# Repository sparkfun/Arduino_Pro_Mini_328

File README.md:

Arduino Pro Mini 328
====================

<table class="table table-hover table-striped table-bordered">
  <tr align="center">
   <td></td>
   <td></td>
  </tr>
  <tr align="center">
    <td><i>Arduino Pro Mini 328 - 5V/16MHz [<a href="https://www.sparkfun.com/products/11113">DEV-11113</a>]</i></td>
    <td><i>Arduino Pro Mini 328 - 3.3V/8MHz [<a href="https://www.sparkfun.com/products/11114">DEV-11114</a>]</i></td>
  </tr>
</table>

SparkFun's Arduino Pro Mini 328 is a bare bones super small Arduino compatible development board. This hardware is used for both the 3.3V/8MHz and the 5V/16MHz versions. 

Both of these products use the same PCB, but are populated with unique voltage regulators and resonators.

Repository Contents
-------------------
* **/Documentation** - SVG and PDF datasheets for the Pro Mini
* **/Hardware** - Eagle design files (Schematic and Board)
* **/Production** - Test bed files and production panel files

Documentation
--------------
* **[Hookup Guide](https://learn.sparkfun.com/tutorials/using-the-arduino-pro-mini-33v)** - Basic hookup guide for the Arduino Pro Mini 3.3V/8MHz. It can be used as a guide with the 5V. The only difference when following the tutorial is selecting the board definition in the Arduino IDE and the voltage levels.

Product Versions
----------------
* [DEV-11113](https://www.sparkfun.com/products/11113)- 5V/16MHz Pro Mini
* [DEV-15254](https://www.sparkfun.com/products/15254)- 5V/16MHz Pro Mini Starter Kit
* [DEV-11114](https://www.sparkfun.com/products/11114)- 3.3V/8MHz Pro Mini
* [DEV-15257](https://www.sparkfun.com/products/15257)- 3.3V/8MHz Pro Mini Starter Kit 

License Information
-------------------
The hardware is released under [Creative Commons Share-alike 3.0](http://creativecommons.org/licenses/by-sa/3.0/).  

Hardware authors: Original Arduino Mini design by Team Arduino

Pro Mini design by Nathan Seidle @ SparkFun Electonics

Revision work by Pete Lewis @ SparkFun Electonics  

Distributed as-is; no warranty is given.

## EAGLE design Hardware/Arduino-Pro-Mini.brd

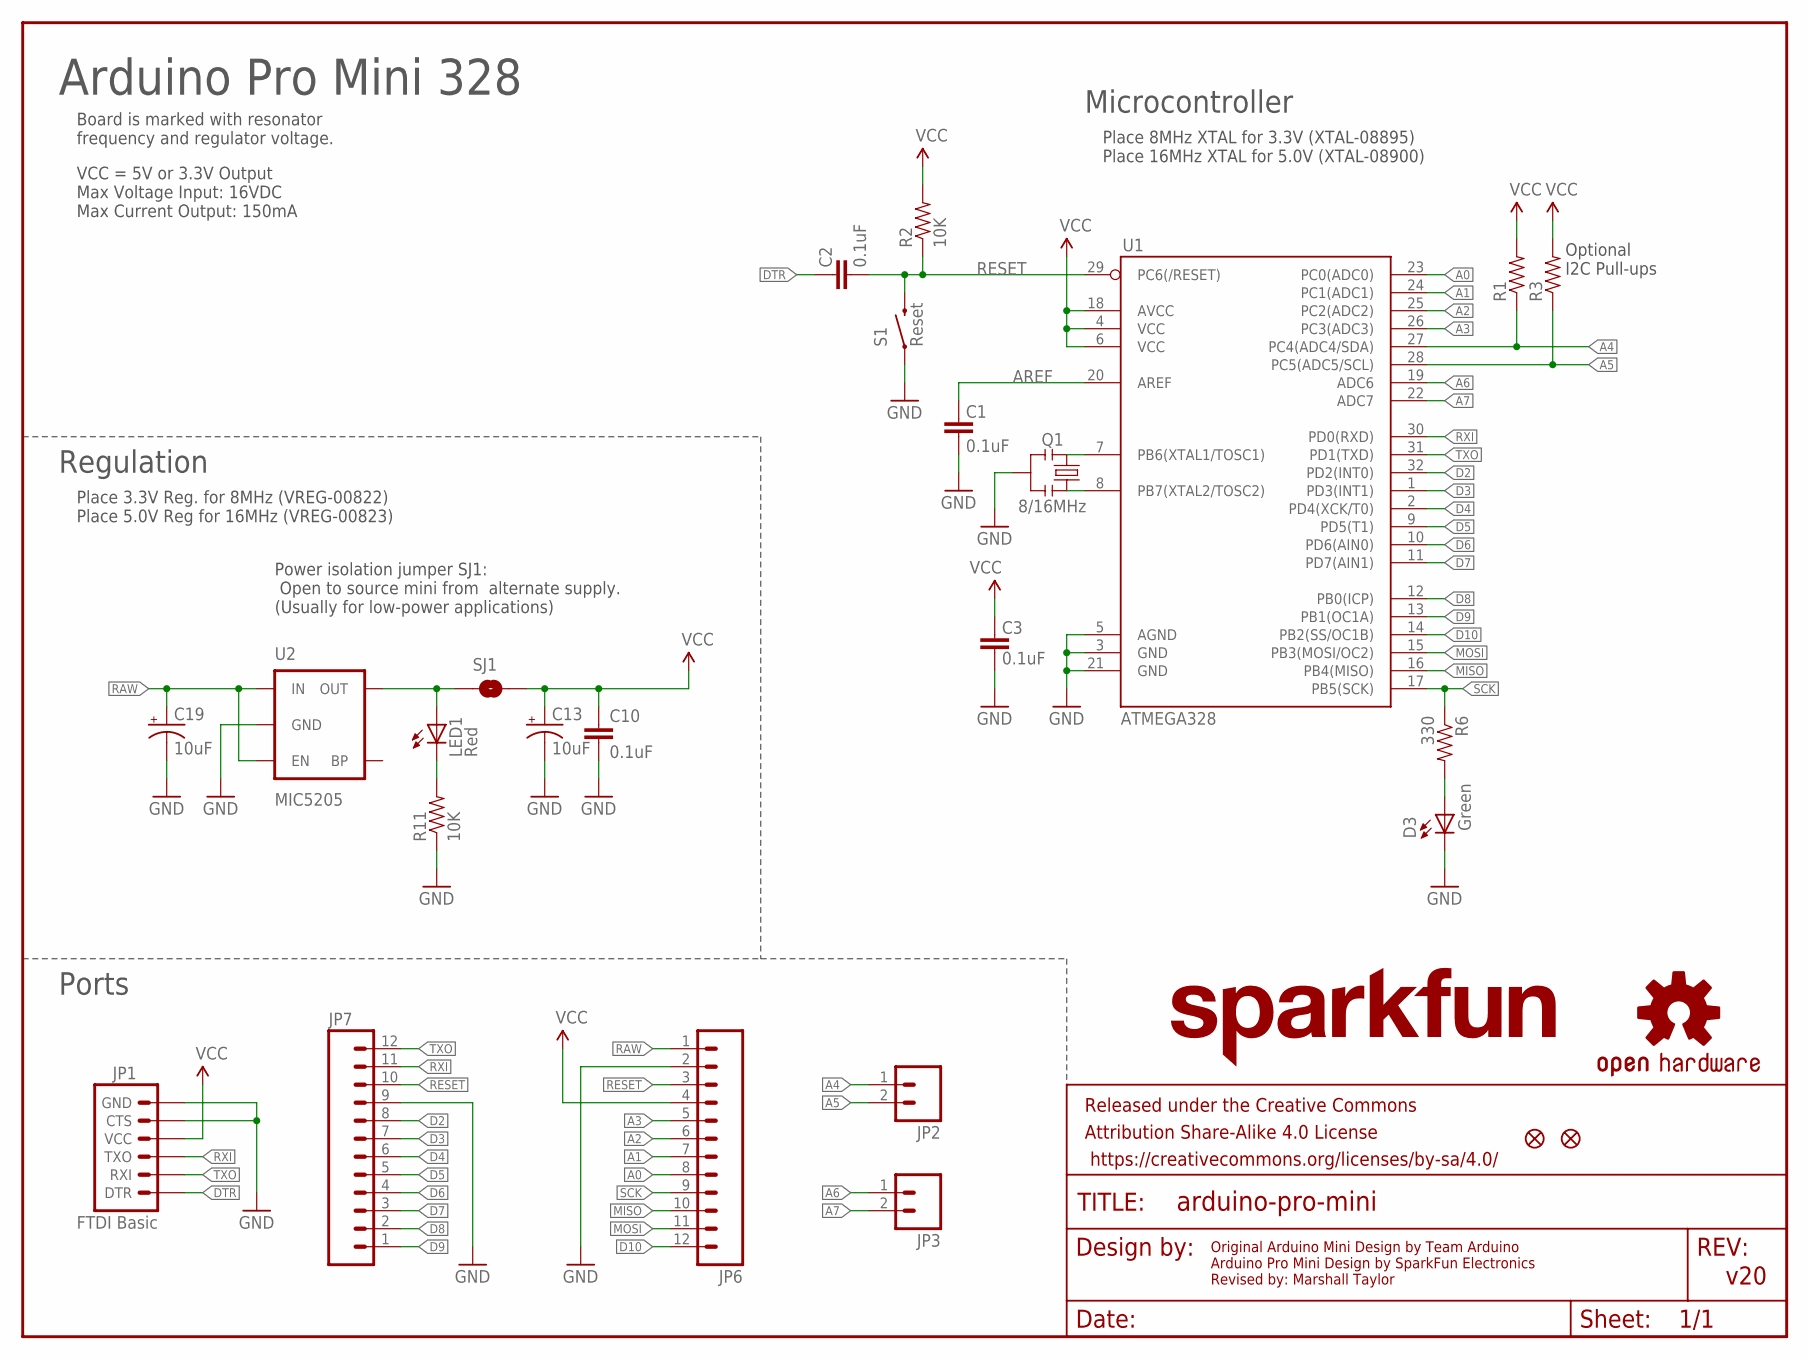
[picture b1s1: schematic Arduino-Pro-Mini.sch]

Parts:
C1, C2, C3, C10: 0.1uF; 0603-CAP
C13, C19: 10uF; EIA3216
D3: Green; 0603-LED-ALT1
FRAME2: FRAME-LETTER; CREATIVE_COMMONS
JP1: FTDI Basic; 1X06
JP2, JP3: M02PTH; 1X02
JP5, JP8: FIDUCIALUFIDUCIAL; MICRO-FIDUCIAL
JP6, JP7: M12PTH; 1X12
LED1: Red; 0603-LED-ALT1
Q1: 8/16MHz; RESONATOR-SMD-1:1
R1, R3: RESISTOR0603-RES; 0603-RES
R2, R11: 10K; 0603-RES
R6: 330; 0603-RES
S1: Reset; TACTILE-SWITCH-SMD-ALT01
SJ1: SOLDERJUMPERNC; SJ_2S
U1: ATMEGA328; TQFP32-08
U2: MIC5205; SOT23-5

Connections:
A0: JP6.8, U1.23 (PC0(ADC0))
A1: JP6.7, U1.24 (PC1(ADC1))
A2: JP6.6, U1.25 (PC2(ADC2))
A3: JP6.5, U1.26 (PC3(ADC3))
A4: JP2.1, R1.1, U1.27 (PC4(ADC4/SDA))
A5: JP2.2, R3.1, U1.28 (PC5(ADC5/SCL))
A6: JP3.1, U1.19 (ADC6)
A7: JP3.2, U1.22 (ADC7)
AREF: C1.2, U1.20 (AREF)
D2: JP7.8, U1.32 (PD2(INT0))
D3: JP7.7, U1.1 (PD3(INT1))
D4: JP7.6, U1.2 (PD4(XCK/T0))
D5: JP7.5, U1.9 (PD5(T1))
D6: JP7.4, U1.10 (PD6(AIN0))
D7: JP7.3, U1.11 (PD7(AIN1))
D8: JP7.2, U1.12 (PB0(ICP))
D9: JP7.1, U1.13 (PB1(OC1A))
D10: JP6.12, U1.14 (PB2(SS/OC1B))
DTR: C2.2, JP1.1 (DTR)
GND: C1.1, C3.1, C10.2, C13.C (-), C19.C (-), D3.C, JP1.5 (CTS), JP1.6 (GND), JP6.2, JP7.9, Q1.2, R11.1, S1.1, S1.2 (1), U1.3 (GND), U1.5 (AGND), U1.21 (GND), U2.2 (GND)
MISO: JP6.10, U1.16 (PB4(MISO))
MOSI: JP6.11, U1.15 (PB3(MOSI/OC2))
unnamed: Q1.3, U1.8 (PB7(XTAL2/TOSC2))
unnamed: Q1.1, U1.7 (PB6(XTAL1/TOSC1))
unnamed: LED1.A, SJ1.1, U2.5 (OUT)
unnamed: LED1.C, R11.2
unnamed: D3.A, R6.2
RAW: C19.A (+), JP6.1, U2.1 (IN), U2.3 (EN)
RESET: C2.1, JP6.3, JP7.10, R2.1, S1.3 (2), S1.4 (2), U1.29 (PC6(/RESET))
RXI: JP1.3 (TXO), JP7.11, U1.30 (PD0(RXD))
SCK: JP6.9, R6.1, U1.17 (PB5(SCK))
TXO: JP1.2 (RXI), JP7.12, U1.31 (PD1(TXD))
VCC: C3.2, C10.1, C13.A (+), JP1.4 (VCC), JP6.4, R1.2, R2.2, R3.2, SJ1.2, U1.4 (VCC), U1.6 (VCC), U1.18 (AVCC)

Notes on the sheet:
Optional I2C Pull-ups
v20
Power isolation jumper SJ1: Open to source mini from alternate supply. (Usually for low-power applications)
Board is marked with resonator frequency and regulator voltage.
Ports
Arduino Pro Mini 328
VCC = 5V or 3.3V Output Max Voltage Input: 16VDC Max Current Output: 150mA
Regulation
Microcontroller
Original Arduino Mini Design by Team Arduino Arduino Pro Mini Design by SparkFun Electronics Revised by: Marshall Taylor
Place 8MHz XTAL for 3.3V (XTAL-08895) Place 16MHz XTAL for 5.0V (XTAL-08900)
Place 3.3V Reg. for 8MHz (VREG-00822) Place 5.0V Reg for 16MHz (VREG-00823)

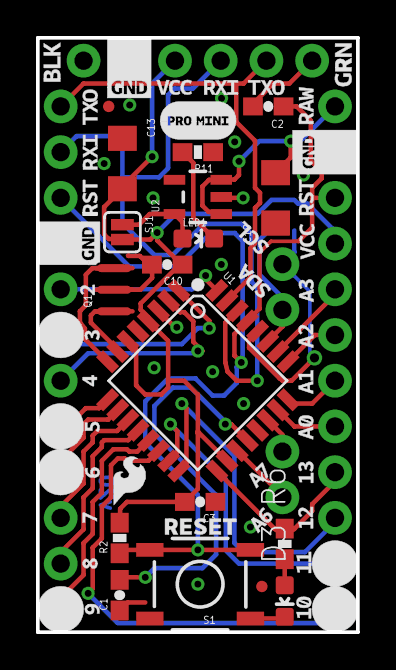
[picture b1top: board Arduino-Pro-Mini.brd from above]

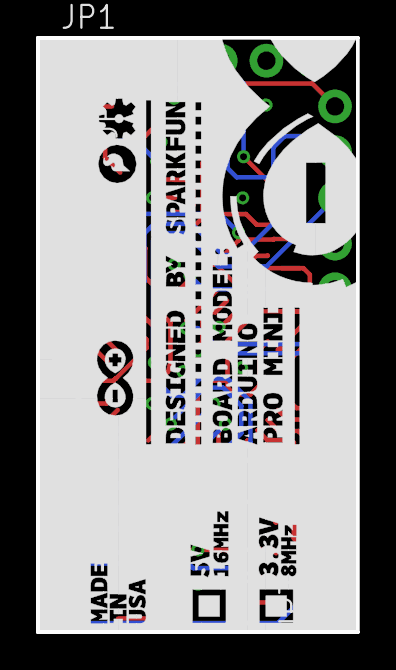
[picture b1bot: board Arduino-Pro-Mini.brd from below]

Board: 2 copper layers, 17.8 x 33.0 mm, 26 parts (7 on the bottom side), 33 nets.

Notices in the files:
parts and their libraries:
SparkFun-Aesthetics: Licensing: CC v3.0 Share-Alike You are welcome to use this library for commercial purposes.
SparkFun-Aesthetics: Released under the Creative Commons Attribution Share-Alike 4.0 License
SparkFun-Aesthetics: https://creativecommons.org/licenses/by-sa/4.0
